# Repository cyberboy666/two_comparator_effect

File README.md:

# two_comparator_effect
### analog video posterisation effect - adapted from a rob schafer design

- this circuit is distributed by __UNDERSCORES__ - _an open video hardware label_ : it is available to purchase - as a pcb, kit or assembled unit - at [underscores.shop](https://underscores.shop/two_comparator_effect/)
- the schematic for the circuit can be found [here](/hardware/schematic.pdf)
- the pcb gerber files for the lastest version can be found [here](/hardware/gerber_latest.zip)
- interactive BOM is [here](https://htmlpreview.github.io/?https://github.com/cyberboy666/two_comparator_effect/blob/main/hardware/bom/ibom.html)
- consider [donating](https://opencollective.com/underscores) to the underscores project to help us continue creating for the commons

## demo video

## background

<details>
<summary>background</summary>

Rob Schafer designed the original version of this circuit in his excellent [whiteboard schoolhouse](https://www.youtube.com/watch?v=9HMj0sfPa0w&list=PLoNU5z_Oqfgj1xfSBMg6XaIhAX2ftyfkN) youtube series.

It was updated and adapted to pcb by cyberboy666 as open-source hardware with help from the [scanlines community](https://scanlines.xyz/t/whiteboard-schoolhouse-companion-circuits/127/23) – this version debuted as a mail-in soldering workshop for [VIDICON_2020](https://vidicon.org/)

robs original circuit, the schematic and effect shown here 

</details>
  
# documentation

this project is fully _open-source hardware_ - all the files required to build it are included in this repo for free. if you have the time and/or skill you can contribute back by collaborating on / testing new designs, improving these docs, making demo videos/other creative content etc. you can also support the project financially by [donating](https://opencollective.com/underscores) directing, or purchasing through the [web shop](https://underscores.shop).

depending on whether you are going fully diy or buying an assembled and tested unit, some of the following guides will be relavent to you. the flow would be:

## ordering parts

<details><summary><b>parts sourcing guide (w/ notes on pcb fabracation )</b> - start here if you are building fully from scatch or have purchased a pcb</summary>

i try to source all the parts i can from either:
- [tayda](https://www.taydaelectronics.com/) ; cheaper for common parts like resistors etc, also good for mechanical parts like switches and buttons
- [mouser](https://www.mouser.de/) ; has lots more options, speciality video ic's, can sometimes cost more (free shipping on orders over 50euros)
- other ; ocationally there will be parts which will need to be sourced elsewhere - usaully either aliexpress, ebay or amazon etc...

take a look at the [full_bom](/hardware/bom/full_bom.csv) for this project to see where i am sourcing each part from

## import into tayda

- go to the [tayda quick order](https://www.taydaelectronics.com/quick-order/) and in bottom corner choose _add from file_
- select the file [tayda_bom.csv](./hardware/bom/tayda_bom.csv) in the BOM folder (you will have to download it first or clone this repo)
- after importing select _add to cart_
- __NOTE:__ the minimum value for resistors is 10, so you may need to modify these values to add to cart (or if they are already modified here you will need to see the  full_bom for actual part QTY) 

- OPTIONAL: it is a good idea to add some dip-ic sockets and 2.54pin headers/sockets to your tayda order if you dont have them around already
  
## import into mouser

- go to [mouser bom tool](https://nz.mouser.com/Bom/) and click _upload spreadsheet_
- select the file [mouser_bom.csv](./hardware/bom/mouser_bom.csv) in this folder (you will have to download it first or clone this repo), then _upload my spreadsheet_ and _next_
- ensure that __Mouser Part Number__ is selected in the dropdown above the first row, then _next_, _process_
- if everything looks correct can now put _add to basket_

# ordering pcbs

you can support this project by buying individual pcbs from the [shop](https://underscores.shop). if you would rather have pcbs fabricated from gerbers directly the file you need is [here](/hardware/gerber_latest.zip)

- i get my pcbs fabricated from [jlcpcb](https://cart.jlcpcb.com/quote) - 5 is the minumum order per design
- upload the zip file with the `add gerber file` button
- the default settings are mostly fine - set the __PCB Qty__ and __PCB Color__ settings (you can check that the file looks correct with pcb veiwer)
- it may be best to combine orders with other pcbs you want to have fab'd since the shipping can cost more than the items - also orginising group buys is a good way to distribute the extra pcbs /costs 
  
i often use jlcpcb because they are reliable, cheap and give you an option of colours. remember though that the cheapest Chinese fab houses are not always the most ethical or environmently friendly - if you can afford it consider supporting local companies. 

  </details>
  
## assembly guide
  
<details><summary><b>assembly guide</b> - start here if you have purchased a diy kit</summary>

## interactive BOM for build guiding

follow this link to view the [interactive BOM](https://htmlpreview.github.io/?https://github.com/cyberboy666/two_comparator_effect/blob/main/hardware/bom/ibom.html)

## general solder advice

- remember to heat pad first (2-3seconds), then add solder, then continue to heat (1-2seconds)

- Checkout the web-comic [soldering is easy](https://mightyohm.com/files/soldercomic/FullSolderComic_EN.pdf) for more soldering advice

## general order of assembly

- in general while assembling i start placing resistors and capacitors first. placing 5 - 10 components at a time and then flipping the board to solder them and trim the legs etc.
- next i would do diodes, transistors and ic's - taking care that these are placed in the right direction (using a ic socket can be useful)
- finally i place the interface parts - rca jacks, power jack, pots and switches - make sure these have lots of solder on for structural stablity

## specific assembly advice

- start with the resistors, taking care place the correct value in the correct footprint (if you are unsure of the value can use an online resistor calculator ) , direction does not matter. Place a few resistors in (as many as you are comfortable with) then solder and trim legs

- next lets do capacitors: 0.1u will say 104, while 1uf will say 105 on them - place them all and solder and trim.

- now lets place diodes and transistors. take note of the direction on the diode - black bar on component matching black bar on footprint. Transistor values are printed on thembe sure not to mix them up ! be careful when soldering the to92 parts the pads are very close - this is the hardest part - i soldered the outer legs first, trimmed these and then soldered inner.

- now lets do the ic/socket -> make sure the direction is correct! place in and fold two corner pins to hold in place, then solder all pins. you can place the ic in now too.

- finally lets place the control parts, starting with the power jack (can use something under the board to balance it while you solder), next place the rca jacks and pots. be generous with the solder here -> this is to strengthen the mechanical connections as well as making electrical ones
  
</details>

## operating guide
  
<details><summary><b>operating guide</b> - start here if you have purchased an assembled unit</summary>

- To set up using the circuit plug an active video source into composite video input and a display into composite video output (flipping the bypass switch should show the raw video source passing through the circuit to the display)

- Next plug in a 5v center-positive power supply into the 2.1mm barrel jack connector – I like to use a usb wall charger for this

- switch the bypass again to activate the circuit - Adjusting the level knobs should change the resulting image – the thresholds control which brightness levels result in white black or gray regions.

- Depending on your display setting either or both knobs fully counter-clockwise can result in glitchy effects, colour bleeds and sync drops

</details>

### more info

<details><summary><b>how the circuit works</b></summary>
  
Watch the youtube videos [Lesson 1 – Comparators](https://www.youtube.com/watch?v=ml8xnRFdcHY) and [Lesson 2 – Clamping](https://www.youtube.com/watch?v=FymrxKLHy6c) by Rob Schafer for full explanation. See full schematics on the project page.
  
This circuit works by using multiple stages of an LM339 - Quad Differential Comparator ic. 

A comparator stage compares the two voltages on its input (plus and minus) and outputs high if plus > minus, low if plus < minus. Since we power the ic with +5v, in this case high is an output of +5v and low is an output of 0v
                                                                                                                                 
comparator plus input is connected to the analog video signal (where higher voltage corresponds to a brighter image)

The minus input is connected to a reference voltage which can be set by turning a potentiometer. varying the pot adjusts the resistance in this voltage divider configuration which in turn varies the voltage supplied as reference
                                                                                                                                 

The result of this effect is an image that is all white for regions of the original image above a given brightness threshold level, and all black for the regions below this level. Changing this threshold changes which parts of the image are set to black vs white.

Here is a scoped example of an original signal (top) with threshold and the resulting signal (bottom)

Before reaching the comparators, the incoming video signal needs to be SOFT CLAMPED – this is done using a capacitor, diode and a 1.25v rail that was obtained with a LM317 voltage regulator.

A composite video signal tends to squash up when the image is bright and spread out when it is darker.

For the comparator reference voltages to be consistence we need to correct for this behavior by clamping the signal to a fixed voltage level
                                                                                                                                 

A third comparator stage with a fixed reference voltage is used to ‘pick off’ the sync pulse of the original signal.

The output from these three comparator stages are scaled and combined to create a new composite video signal with the desired effect
                                                                                                                                 

Composite video encodes color as a sub-carrier frequency over the signal.

This circuit is designed for use with gray-scale video input where no sub-carrier is present, although it does still work with color input – usually ignoring the _sub-carrier_, although occasionally there are some artifacts generated by this. This is more common with NTSC than with PAL

glitch artifacts are also created when the comparator thresholds are set below the _black-level_ of the video signal, causing the signal to lose sync. 
                                                                                                                             
</details>

<details><summary><b>contributing guide</b></summary>
  
if you would like to contribute back to these projects in some way but dont know how the best thing (for now) would be to reach out to me directly ( tim@cyberboy666.com or @cyberboy666 on scanlines forum) - i will be happy to help
  
</details>

## credits & more info

This circuit is distributed through UNDERSCORES – open video hardware label – visit [underscores.shop](https://underscores.shop) for more info

The pcb was designed using KICAD , the booklet was created in LibreOffice Draw

Everything from gerbers, cad files, panels and documentation is freely available online and distributed under CC-BY-SA / open-source licenses – help us contribute to the commons !

Ask any questions or start discussions related to this project on the [scanlines.xyz](https://scanlines.xyz) forum – an online community space dedicated to diy av / electronic media art

You can contact me directly at tim (at) cyberboy666 (dot) com 
Please get in touch if you are interested in hosting a workshop !

Thanks to Rob Schafer for sharing your designs and knowledge. to Bastien Lavaud for circuit advice, always. To Guergana Tzatchkova for booklet design inspiration. To Ben Caldwell for project advice. To everyone who has or will contribute ♥♥♥

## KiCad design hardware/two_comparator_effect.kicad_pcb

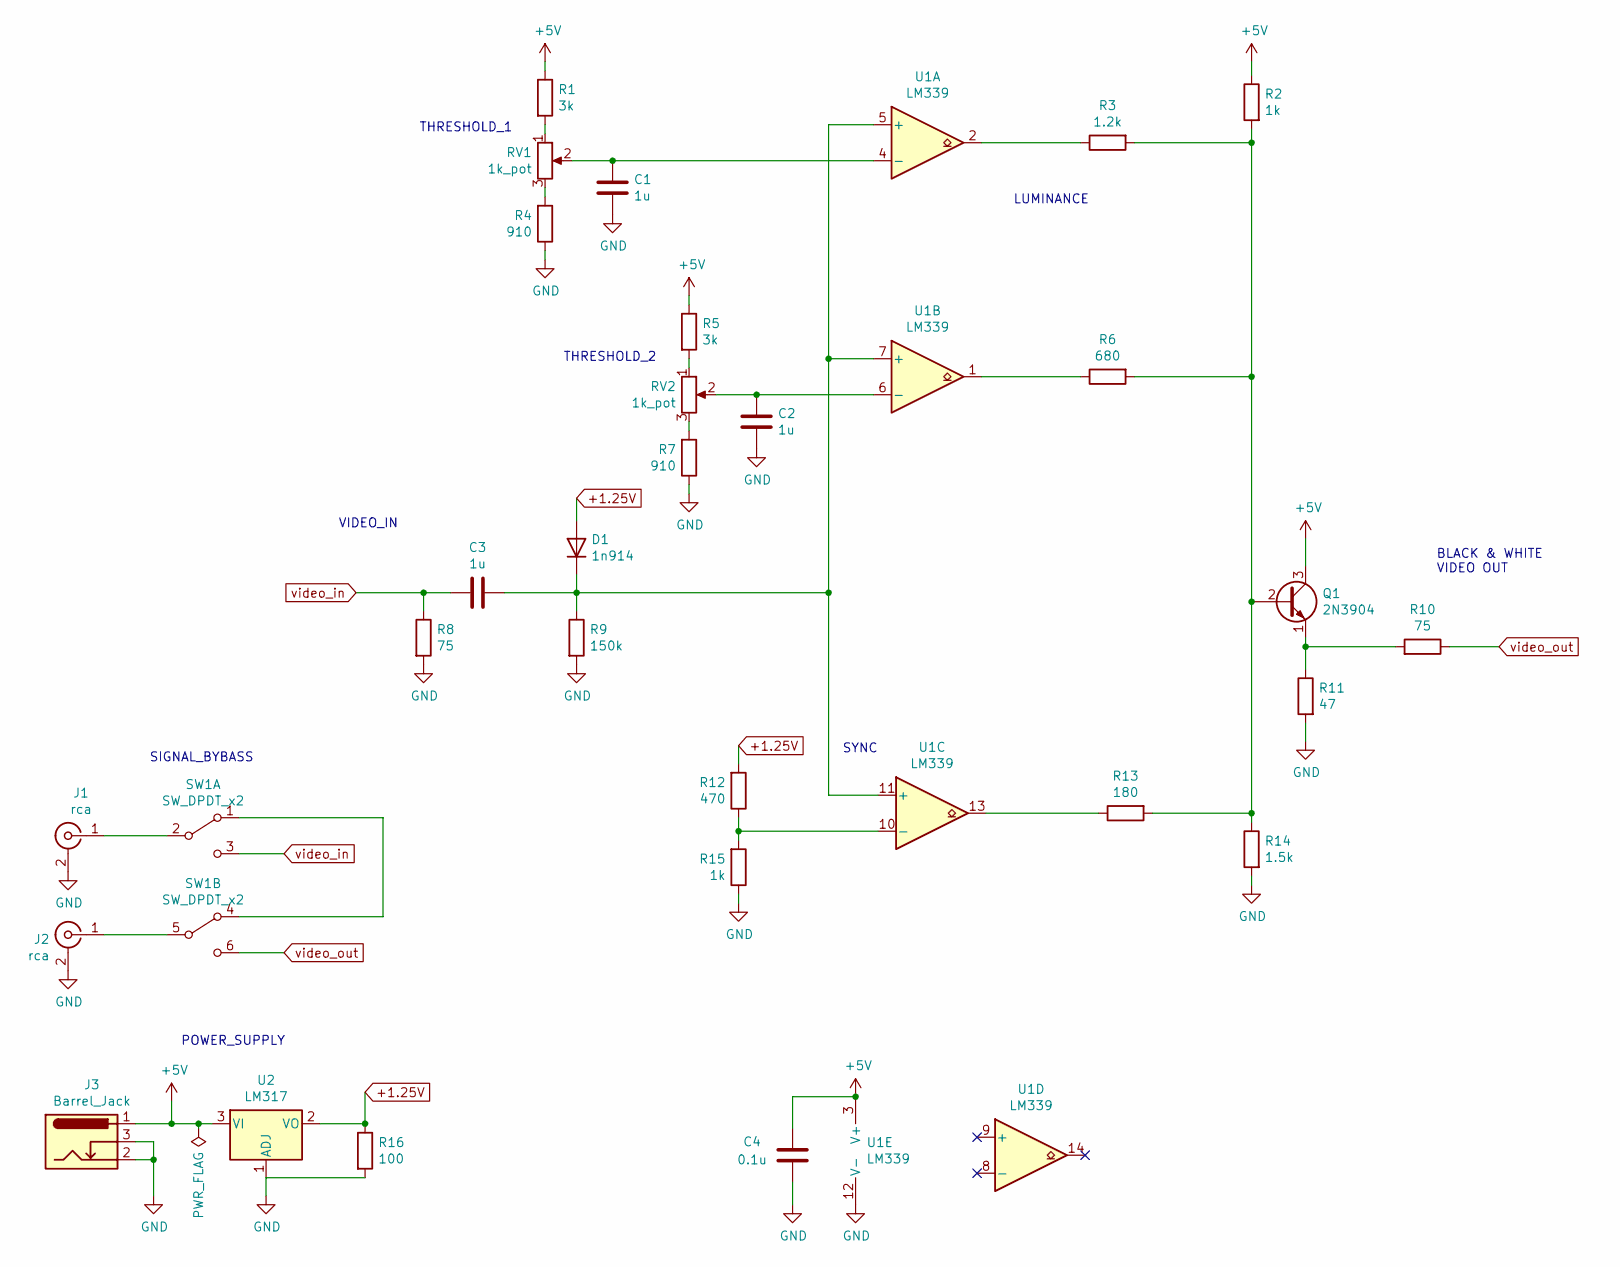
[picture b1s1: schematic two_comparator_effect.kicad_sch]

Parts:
C1, C2, C3: 1u; C_Disc_D4.7mm_W2.5mm_P5.00mm
C4: 0.1u; C_Disc_D4.7mm_W2.5mm_P5.00mm
D1: 1n914; D_A-405_P7.62mm_Horizontal
J1, J2: rca; tht_rca_vertical
J3: Barrel_Jack; BarrelJack_Horizontal
Q1: 2N3904; TO-92_HandSolder
R1, R5: 3k; R_Axial_DIN0207_L6.3mm_D2.5mm_P7.62mm_Horizontal
R2, R15: 1k; R_Axial_DIN0207_L6.3mm_D2.5mm_P7.62mm_Horizontal
R3: 1.2k; R_Axial_DIN0207_L6.3mm_D2.5mm_P7.62mm_Horizontal
R4, R7: 910; R_Axial_DIN0207_L6.3mm_D2.5mm_P7.62mm_Horizontal
R6: 680; R_Axial_DIN0207_L6.3mm_D2.5mm_P7.62mm_Horizontal
R8, R10: 75; R_Axial_DIN0207_L6.3mm_D2.5mm_P7.62mm_Horizontal
R9: 150k; R_Axial_DIN0207_L6.3mm_D2.5mm_P7.62mm_Horizontal
R11: 47; R_Axial_DIN0207_L6.3mm_D2.5mm_P7.62mm_Horizontal
R12: 470; R_Axial_DIN0207_L6.3mm_D2.5mm_P7.62mm_Horizontal
R13: 180; R_Axial_DIN0207_L6.3mm_D2.5mm_P7.62mm_Horizontal
R14: 1.5k; R_Axial_DIN0207_L6.3mm_D2.5mm_P7.62mm_Horizontal
R16: 100; R_Axial_DIN0207_L6.3mm_D2.5mm_P7.62mm_Horizontal
RV1, RV2: 1k_pot; Potentiometer_Vertical_Large
SW1: SW_DPDT_x2; dpdt_mini_toggle_switch_tayda
U1: LM339; DIP-14_W7.62mm_LongPads
U2: LM317; TO-92_Inline

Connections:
+1.25V: D1.2 (A), R12.2, R16.1, U2.2 (VO)
+5V: C4.1, J3.1, Q1.3 (C), R1.1, R2.1, R5.1, U1.3 (V+), U2.3 (VI)
GND: C1.1, C2.1, C4.2, J1.2 (Ext), J2.2 (Ext), J3.2, J3.3, R4.1, R7.1, R8.2, R9.2, R11.2, R14.2, R15.1, R16.2, U1.12 (V-), U2.1 (ADJ)
unnamed: C1.2, RV1.2, U1.4 (-)
unnamed: C2.2, RV2.2, U1.6 (-)
unnamed: C3.1, D1.1 (K), R9.1, U1.5 (+), U1.7 (+), U1.11 (+)
unnamed: J1.1 (In), SW1.2 (B)
unnamed: J2.1 (In), SW1.5 (B)
unnamed: Q1.1 (E), R10.2, R11.1
unnamed: Q1.2 (B), R2.2, R3.2, R6.2, R13.2, R14.1
unnamed: R1.2, RV1.1
unnamed: R3.1, U1.2
unnamed: R4.2, RV1.3
unnamed: R5.2, RV2.1
unnamed: R6.1, U1.1
unnamed: R7.2, RV2.3
unnamed: R12.1, R15.2, U1.10 (-)
unnamed: R13.1, U1.13
unnamed: SW1.1 (A), SW1.4 (A)
video_in: C3.2, R8.1, SW1.3 (C)
video_out: R10.1, SW1.6 (C)

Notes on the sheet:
THRESHOLD_2
BLACK & WHITE VIDEO OUT
POWER_SUPPLY
THRESHOLD_1
SYNC
VIDEO_IN
SIGNAL_BYBASS
LUMINANCE

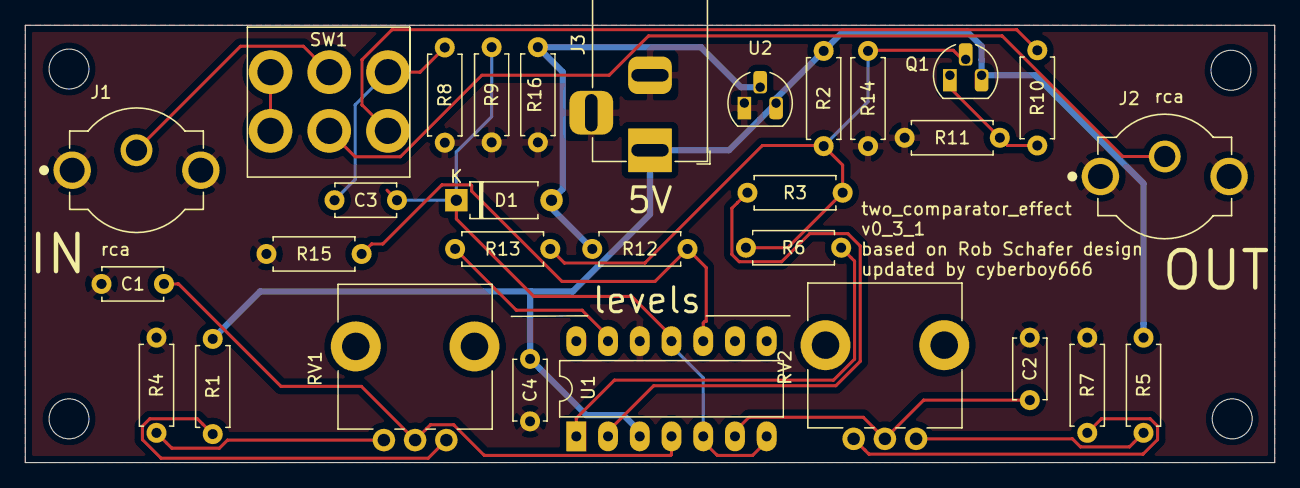
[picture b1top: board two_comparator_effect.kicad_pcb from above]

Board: 2 copper layers, 100.0 x 35.0 mm, 30 parts (0 on the bottom side), 21 nets.

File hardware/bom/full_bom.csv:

sku,qty,ref,val,vendor
A-321,3,C1 C2 C3 ,1u,tayda
A-4008,1,C4 ,0.1u,tayda
A-615,1,D1 ,1n914,tayda
490-RCJ-024,2,J1 J2 ,rca,mouser
A-4118,1,J3 ,Barrel_Jack,tayda
A-111,1,Q1 ,2N3904,tayda
A-2349,2,R1 R5 ,3k,tayda
A-2190,1,R11 ,47,tayda
A-2247,1,R12 ,470,tayda
A-2278,1,R13 ,180,tayda
A-2202,1,R14 ,1.5k,tayda
A-2245,1,R16 ,100,tayda
A-2200,2,R2 R15 ,1k,tayda
A-2201,1,R3 ,1.2k,tayda
A-2623,2,R4 R7 ,910,tayda
A-2281,1,R6 ,680,tayda
A-2193,2,R8 R10 ,75,tayda
A-2210,1,R9 ,150k,tayda
A-1863,2,RV1 RV2 ,1k_pot,tayda
A-4568,1,SW1 ,SW_DPDT_x2,tayda
A-022,1,U1 ,LM339,tayda
A-500,1,U2 ,LM317,tayda

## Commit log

2022-01-10 migrate repo
2022-01-10 folder restructure
2022-01-17 Rename README.md to README_old.md
2022-01-17 repo refactor
2022-01-17 Create parts_sourcing_guide
2022-01-17 Rename parts_sourcing_guide to parts_sourcing_guide.md
2022-01-19 refactor files
2022-01-19 adding csv files
2022-01-30 more refactor files
2022-01-31 update booklet
2022-01-31 adding gitattribures
2022-01-31 Rename .gitattributes to .gitattributesxxx
2022-02-09 rename schamtic
2022-02-10 add 3d model
2022-02-22 lastest gerber
2022-02-28 update bom
2022-09-19 changed theshold resistor values
2022-09-20 update booklet format
2023-07-12 add panel stuff
2024-05-19 add git attribute
